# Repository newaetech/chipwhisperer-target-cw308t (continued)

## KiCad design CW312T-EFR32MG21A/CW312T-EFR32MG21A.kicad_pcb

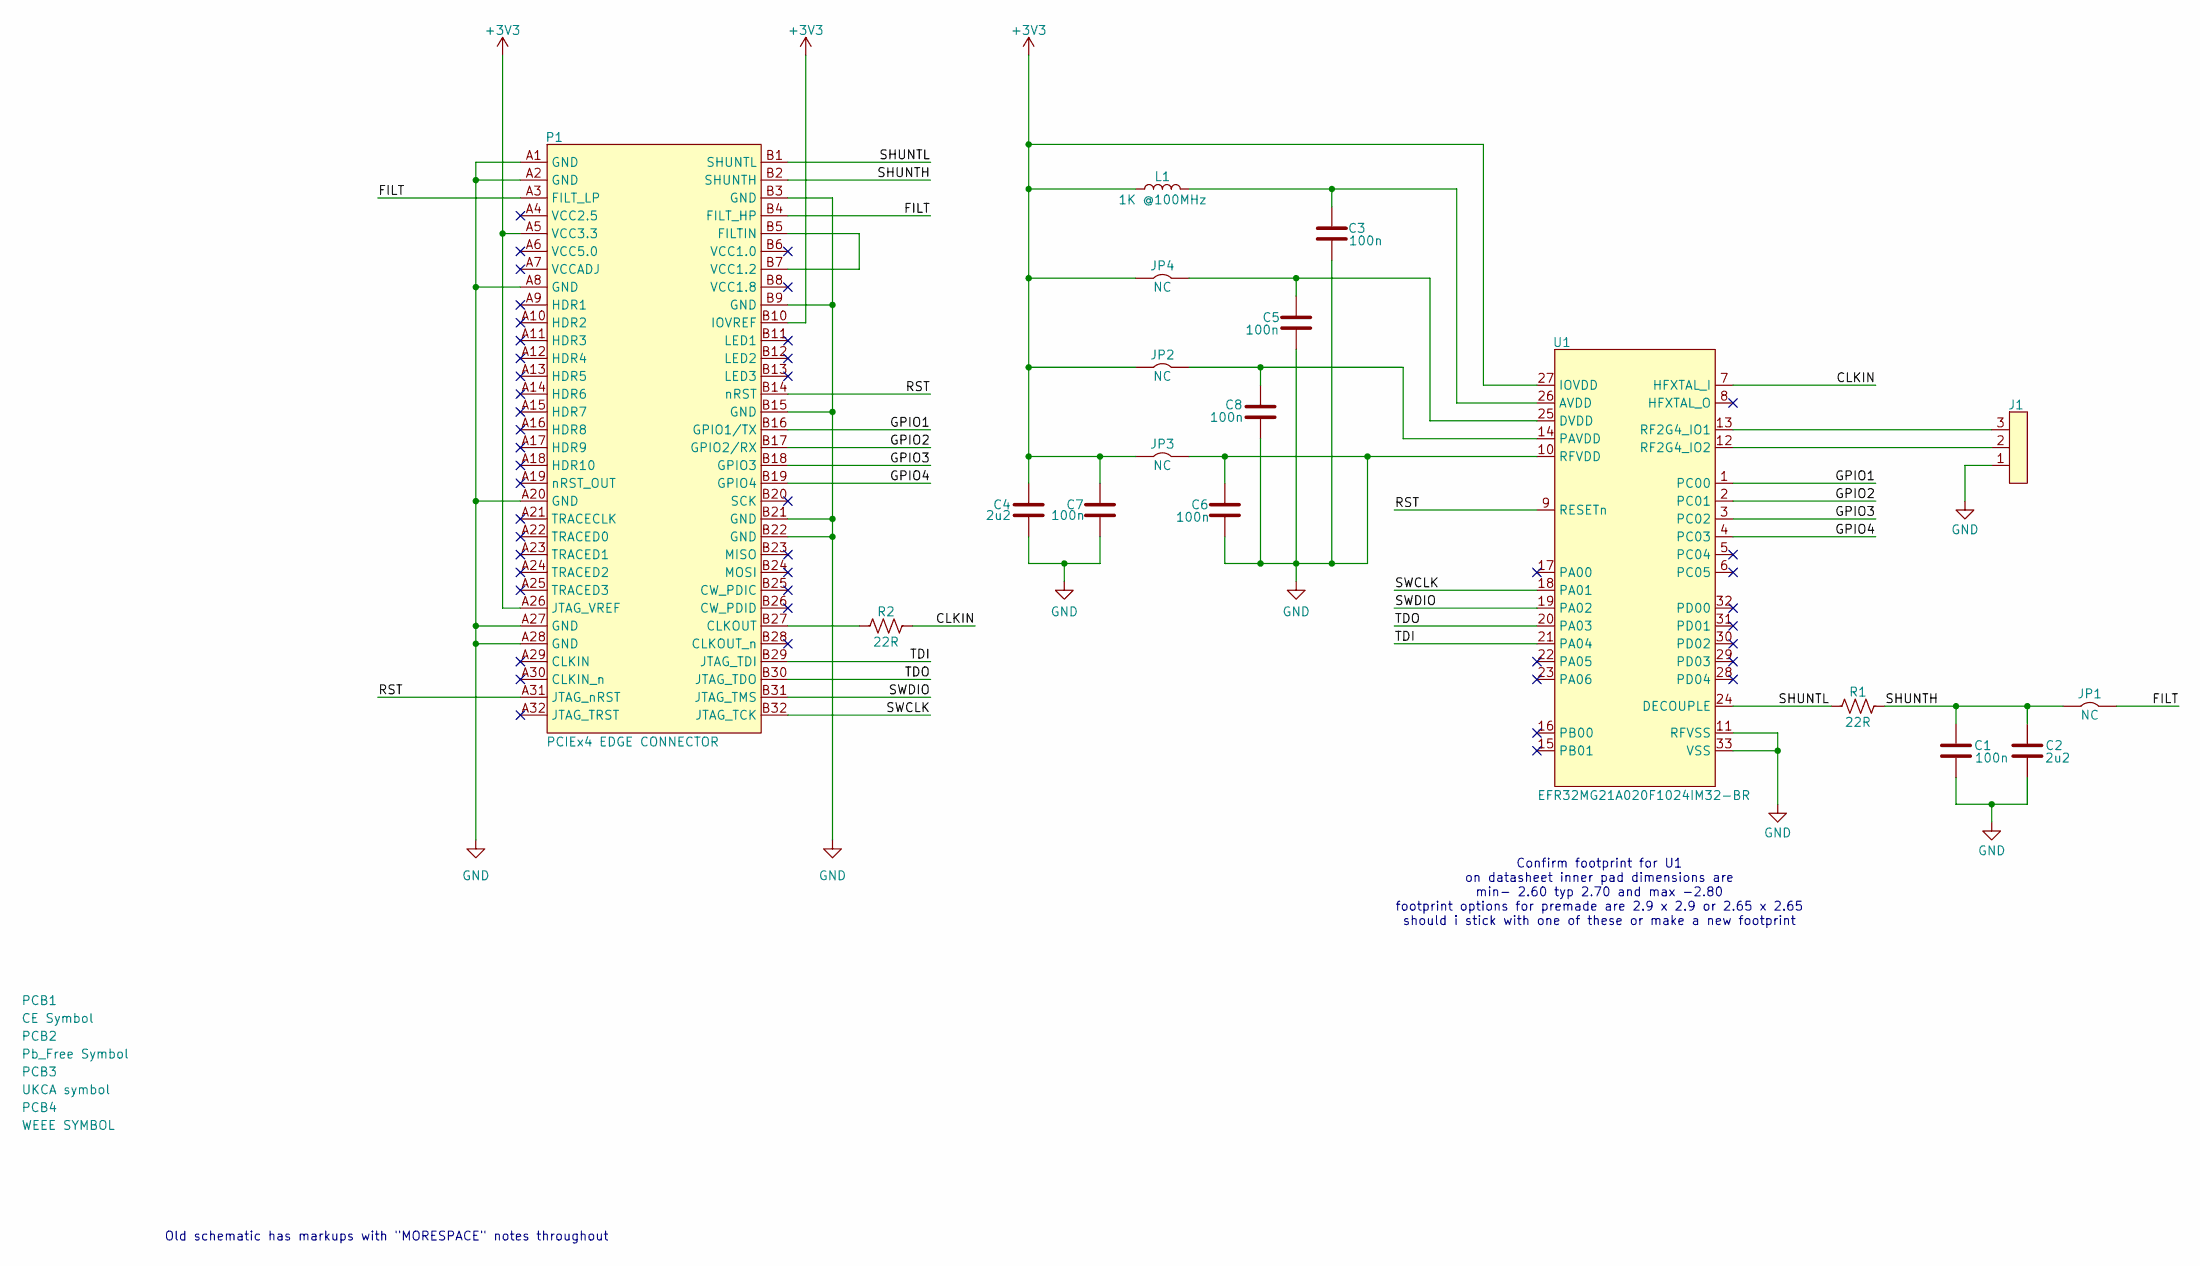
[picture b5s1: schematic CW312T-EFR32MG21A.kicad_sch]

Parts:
C1, C3, C5, C6, C7, C8: CAP_100n_10V_0603; C_0603_1608Metric; Manufacturer Part Number CC0603KRX7R6BB104
C2, C4: CAP_2u2_10V_0603; C_0603_1608Metric; Manufacturer Part Number CC0603KPX7R6BB225
J1: 1x3 straight header pins; PinHeader_1x03_P2.54mm_Vertical; Manufacturer Part Number 61300311121
JP1, JP2, JP3, JP4: SolderJumper-2_P1.3mm_Bridged2Bar_Pad1.0x1.5mm
L1: IND_1K_0603; L_0603_1608Metric; Manufacturer Part Number FBMH1608HM102-T
P1: PCIEx4 EDGE CONNECTOR; CW312_Template
PCB1: CE Symbol; CE-Logo_8.5x6mm_SilkScreen
PCB2: Pb_Free Symbol; Pb_Free_8.0x8.0mm_SilkScreen
PCB3: UKCA symbol; UKCA-Logo_8x8mm_SilkScreen
PCB4: WEEE SYMBOL; WEEE-Logo_5.6x8mm_SilkScreen
R1, R2: RES_22R_0603; R_0603_1608Metric; Manufacturer Part Number RC0603FR-0722RL
U1: EFR32MG21A020F1024IM32-BR; QFN-32-1EP_4x4mm_P0.4mm_EP2.9x2.9mm; Manufacturer Part Number EFR32MG21A020F1024IM32-BR

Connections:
+3V3: C4.2, C7.2, JP2.2, JP3.2, JP4.2, L1.1, P1.A5 (VCC3.3), P1.A26 (JTAG_VREF), P1.B10 (IOVREF), U1.27 (IOVDD)
/CLKIN: R2.2, U1.7 (HFXTAL_I)
/FILT: JP1.1, P1.A3 (FILT_LP), P1.B4 (FILT_HP)
/GPIO1: P1.B16 (GPIO1/TX), U1.1 (PC00)
/GPIO2: P1.B17 (GPIO2/RX), U1.2 (PC01)
/GPIO3: P1.B18 (GPIO3), U1.3 (PC02)
/GPIO4: P1.B19 (GPIO4), U1.4 (PC03)
/RST: P1.A31 (JTAG_nRST), P1.B14 (nRST), U1.9 (RESETn)
/SHUNTH: C1.2, C2.2, JP1.2, P1.B2 (SHUNTH), R1.2
/SHUNTL: P1.B1 (SHUNTL), R1.1, U1.24 (DECOUPLE)
/SWCLK: P1.B32 (JTAG_TCK), U1.18 (PA01)
/SWDIO: P1.B31 (JTAG_TMS), U1.19 (PA02)
/TDI: P1.B29 (JTAG_TDI), U1.21 (PA04)
/TDO: P1.B30 (JTAG_TDO), U1.20 (PA03)
GND: C1.1, C2.1, C3.1, C4.1, C5.1, C6.1, C6.2, C7.1, C8.1, J1.1, JP3.1, P1.A1 (GND), P1.A2 (GND), P1.A8 (GND), P1.A20 (GND), P1.A27 (GND), P1.A28 (GND), P1.B3 (GND), P1.B9 (GND), P1.B15 (GND), P1.B21 (GND), P1.B22 (GND), U1.10 (RFVDD), U1.11 (RFVSS), U1.33 (VSS)
unnamed: P1.B27 (CLKOUT), R2.1
unnamed: P1.B5 (FILTIN), P1.B7 (VCC1.2)
unnamed: C3.2, L1.2, U1.26 (AVDD)
unnamed: C5.2, JP4.1, U1.25 (DVDD)
unnamed: C8.2, JP2.1, U1.14 (PAVDD)
unnamed: J1.3, U1.13 (RF2G4_IO1)
unnamed: J1.2, U1.12 (RF2G4_IO2)

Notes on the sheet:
Old schematic has markups with "MORESPACE" notes throughout
Confirm footprint for U1 on datasheet inner pad dimensions are min- 2.60 typ 2.70 and max -2.80 footprint options for premade are 2.9 x 2.9 or 2.65 x 2.65 should i stick with one of these or make a new footprint

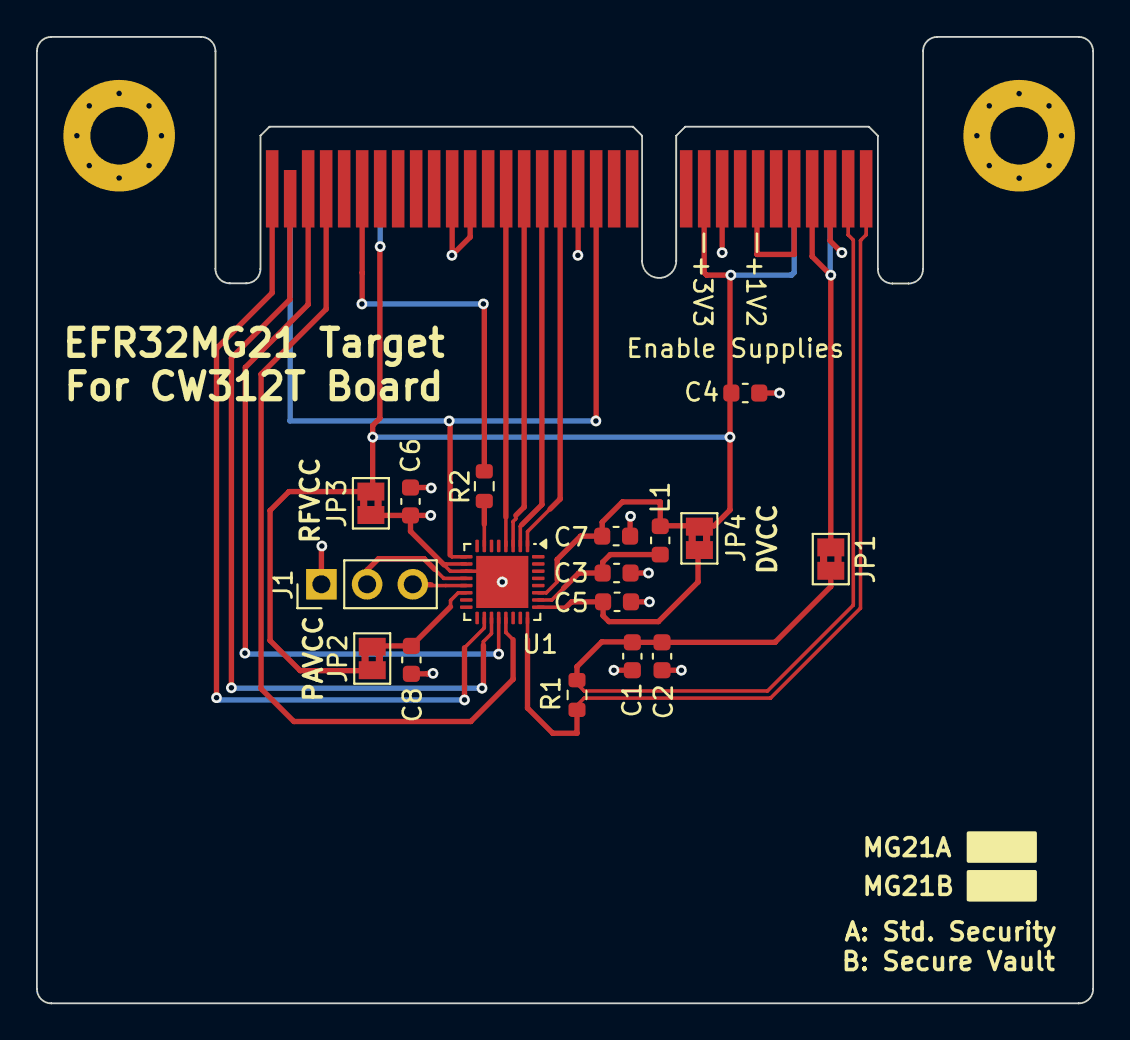
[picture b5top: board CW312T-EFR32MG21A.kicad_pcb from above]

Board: 2 copper layers, 58.7 x 53.7 mm, 22 parts (0 on the bottom side), 22 nets.

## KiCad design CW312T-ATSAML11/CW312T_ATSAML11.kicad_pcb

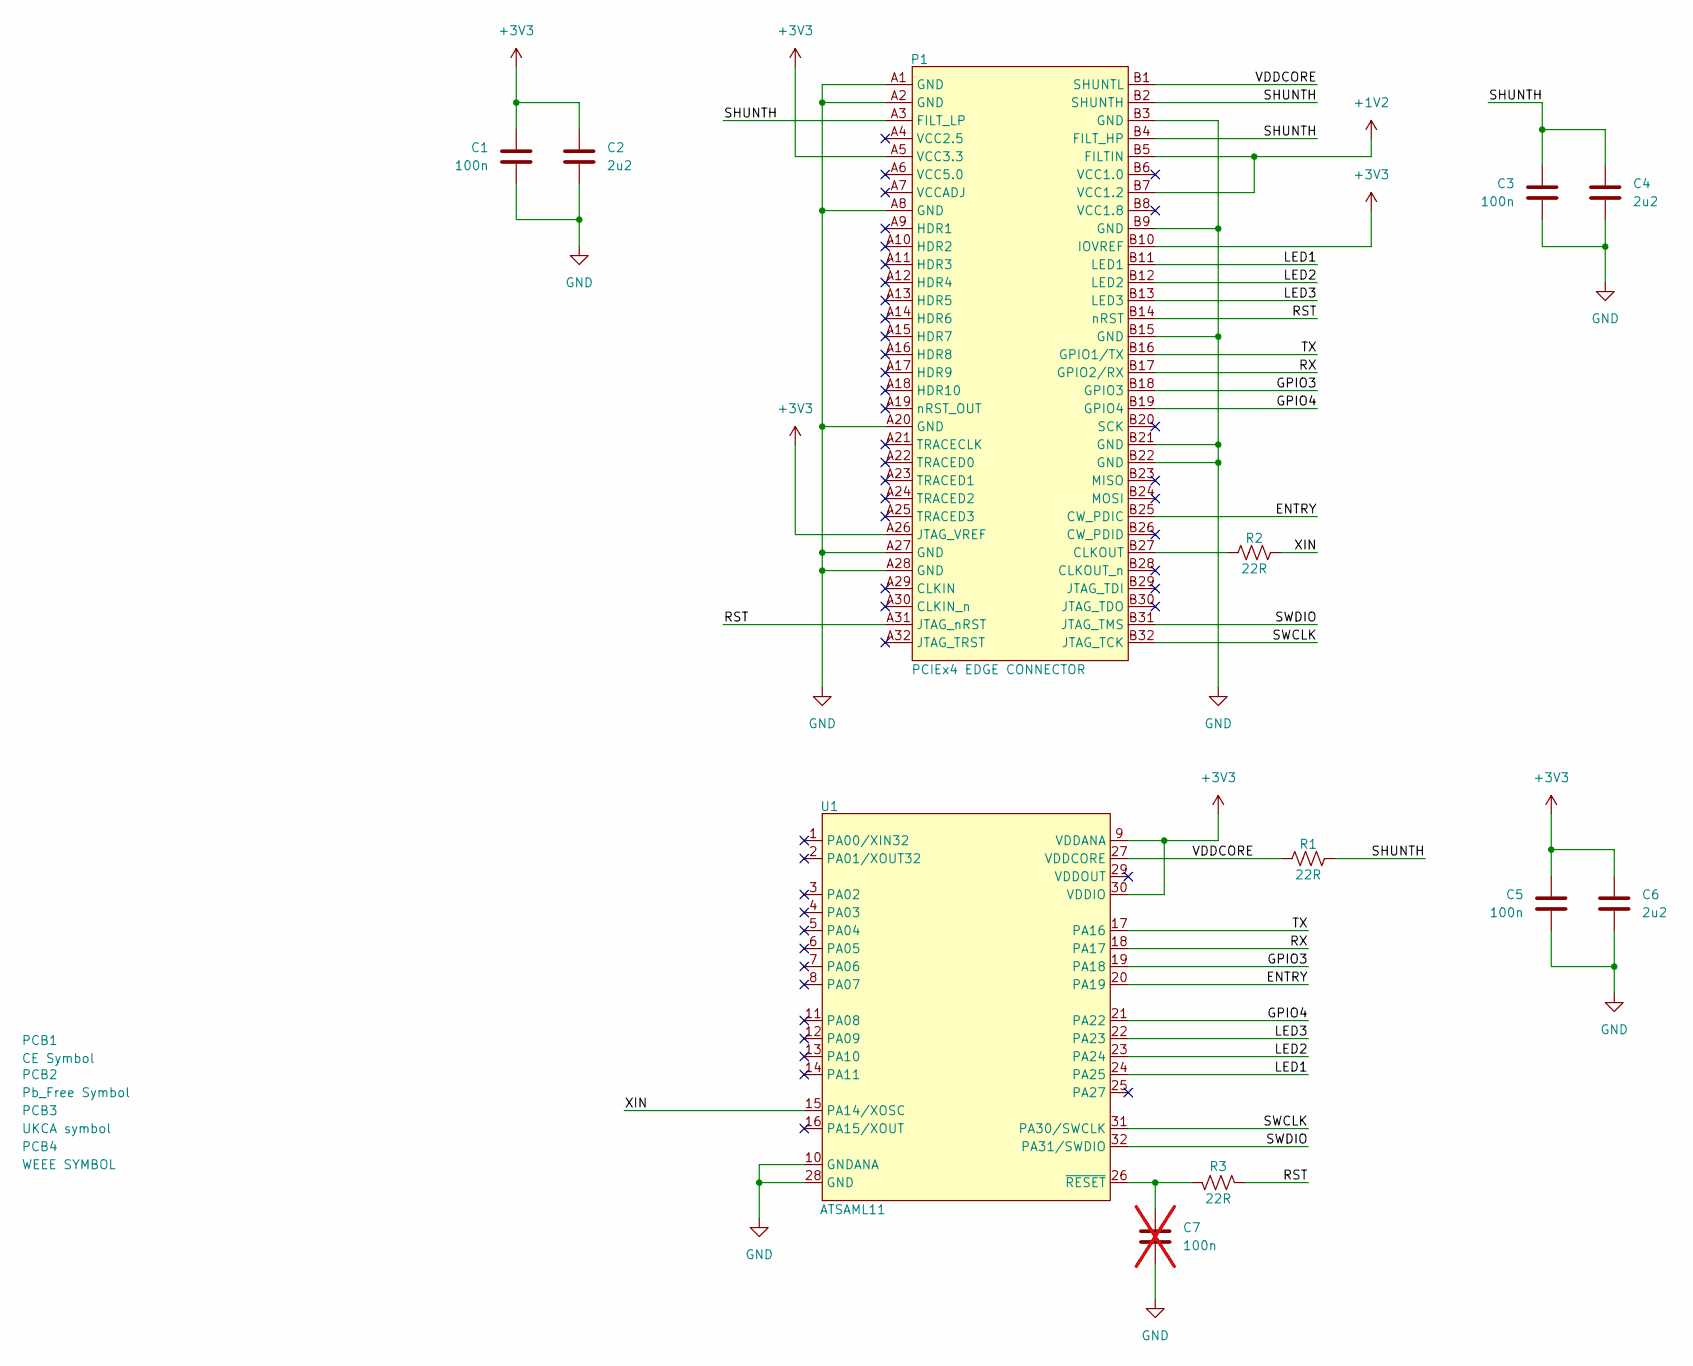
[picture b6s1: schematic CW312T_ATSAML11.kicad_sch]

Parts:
C1, C3, C5: CAP_100n_50V_0603; C_0603_1608Metric; Manufacturer Part Number C0603C104M5RACTU
C2, C4, C6: CAP_2u2_16V_0603; C_0603_1608Metric; Manufacturer Part Number C0603C225K4PAC7867
C7: CAP_100n_50V_0603; C_0603_1608Metric; Manufacturer Part Number C0603C104M5RACTU; not fitted
P1: PCIEx4 EDGE CONNECTOR; CW312_Template
PCB1: CE Symbol; CE-Logo_8.5x6mm_SilkScreen
PCB2: Pb_Free Symbol; Pb_Free_8.0x8.0mm_SilkScreen
PCB3: UKCA symbol; UKCA-Logo_8x8mm_SilkScreen
PCB4: WEEE SYMBOL; WEEE-Logo_5.6x8mm_SilkScreen
R1, R2, R3: 22R_0603; R_0603_1608Metric; Manufacturer Part Number RC0603JR-0722RL
U1: ATSMAL11E16A-AU; TQFP-32_7x7mm_P0.8mm; Manufacturer Part Number ATSAML11E16A-AU

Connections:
+1V2: P1.B5 (FILTIN), P1.B7 (VCC1.2)
+3V3: C1.1, C2.1, C5.1, C6.1, P1.A5 (VCC3.3), P1.A26 (JTAG_VREF), P1.B10 (IOVREF), U1.9 (VDDANA), U1.30 (VDDIO)
/ENTRY: P1.B25 (CW_PDIC), U1.20 (PA19)
/GPIO3: P1.B18 (GPIO3), U1.19 (PA18)
/GPIO4: P1.B19 (GPIO4), U1.21 (PA22)
/LED1: P1.B11 (LED1), U1.24 (PA25)
/LED2: P1.B12 (LED2), U1.23 (PA24)
/LED3: P1.B13 (LED3), U1.22 (PA23)
/RST: P1.A31 (JTAG_nRST), P1.B14 (nRST), R3.2
/RX: P1.B17 (GPIO2/RX), U1.18 (PA17)
/SHUNTH: C3.1, C4.1, P1.A3 (FILT_LP), P1.B2 (SHUNTH), P1.B4 (FILT_HP), R1.2
/SWCLK: P1.B32 (JTAG_TCK), U1.31 (PA30/SWCLK)
/SWDIO: P1.B31 (JTAG_TMS), U1.32 (PA31/SWDIO)
/TX: P1.B16 (GPIO1/TX), U1.17 (PA16)
/VDDCORE: P1.B1 (SHUNTL), R1.1, U1.27 (VDDCORE)
/XIN: R2.2, U1.15 (PA14/XOSC)
GND: C1.2, C2.2, C3.2, C4.2, C5.2, C6.2, C7.2, P1.A1 (GND), P1.A2 (GND), P1.A8 (GND), P1.A20 (GND), P1.A27 (GND), P1.A28 (GND), P1.B3 (GND), P1.B9 (GND), P1.B15 (GND), P1.B21 (GND), P1.B22 (GND), U1.10 (GNDANA), U1.28 (GND)
unnamed: P1.B27 (CLKOUT), R2.1
unnamed: C7.1, R3.1, U1.26 (~RESET)

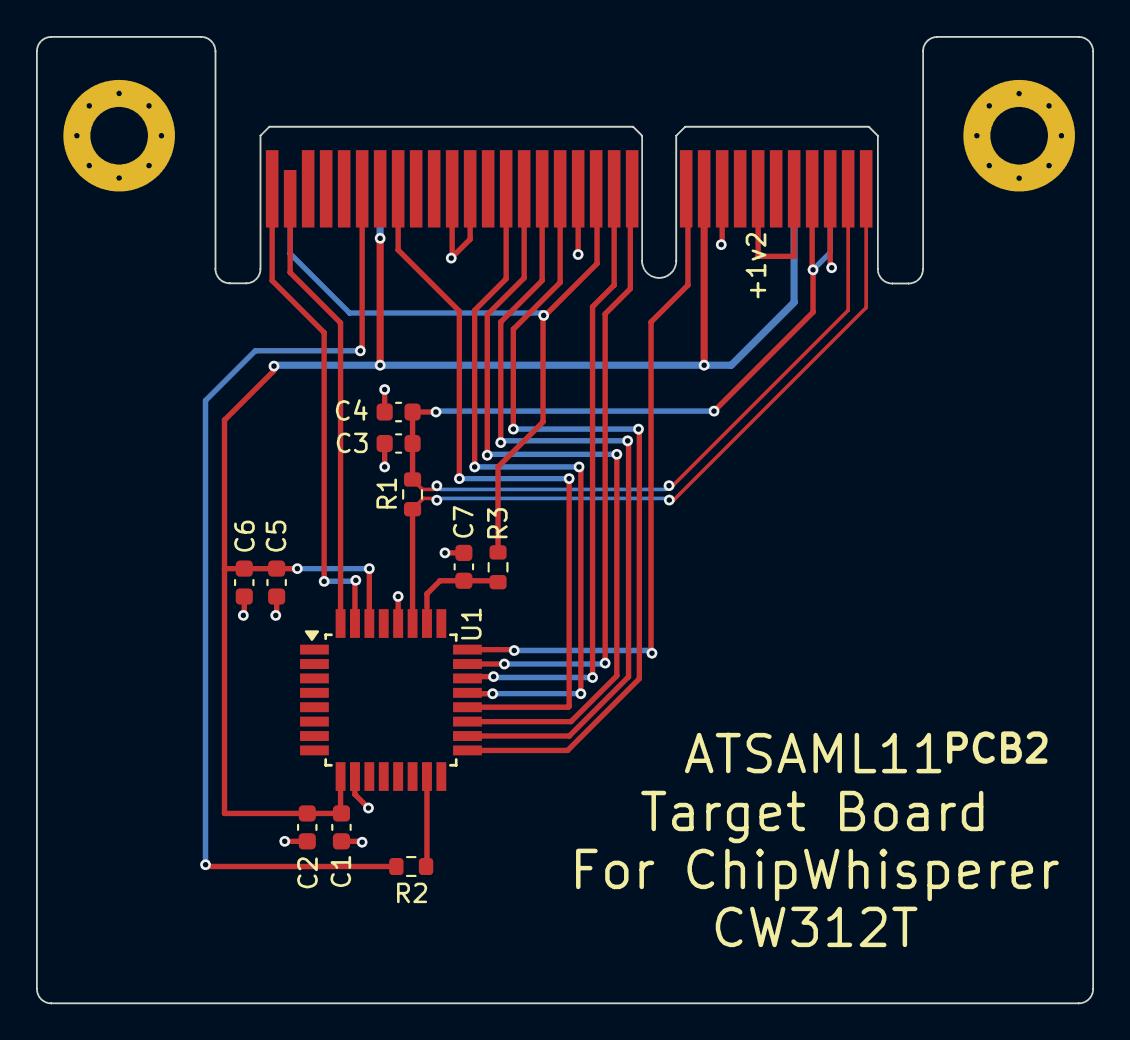
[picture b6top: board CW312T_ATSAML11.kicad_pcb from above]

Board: 2 copper layers, 58.7 x 53.7 mm, 16 parts (0 on the bottom side), 19 nets.

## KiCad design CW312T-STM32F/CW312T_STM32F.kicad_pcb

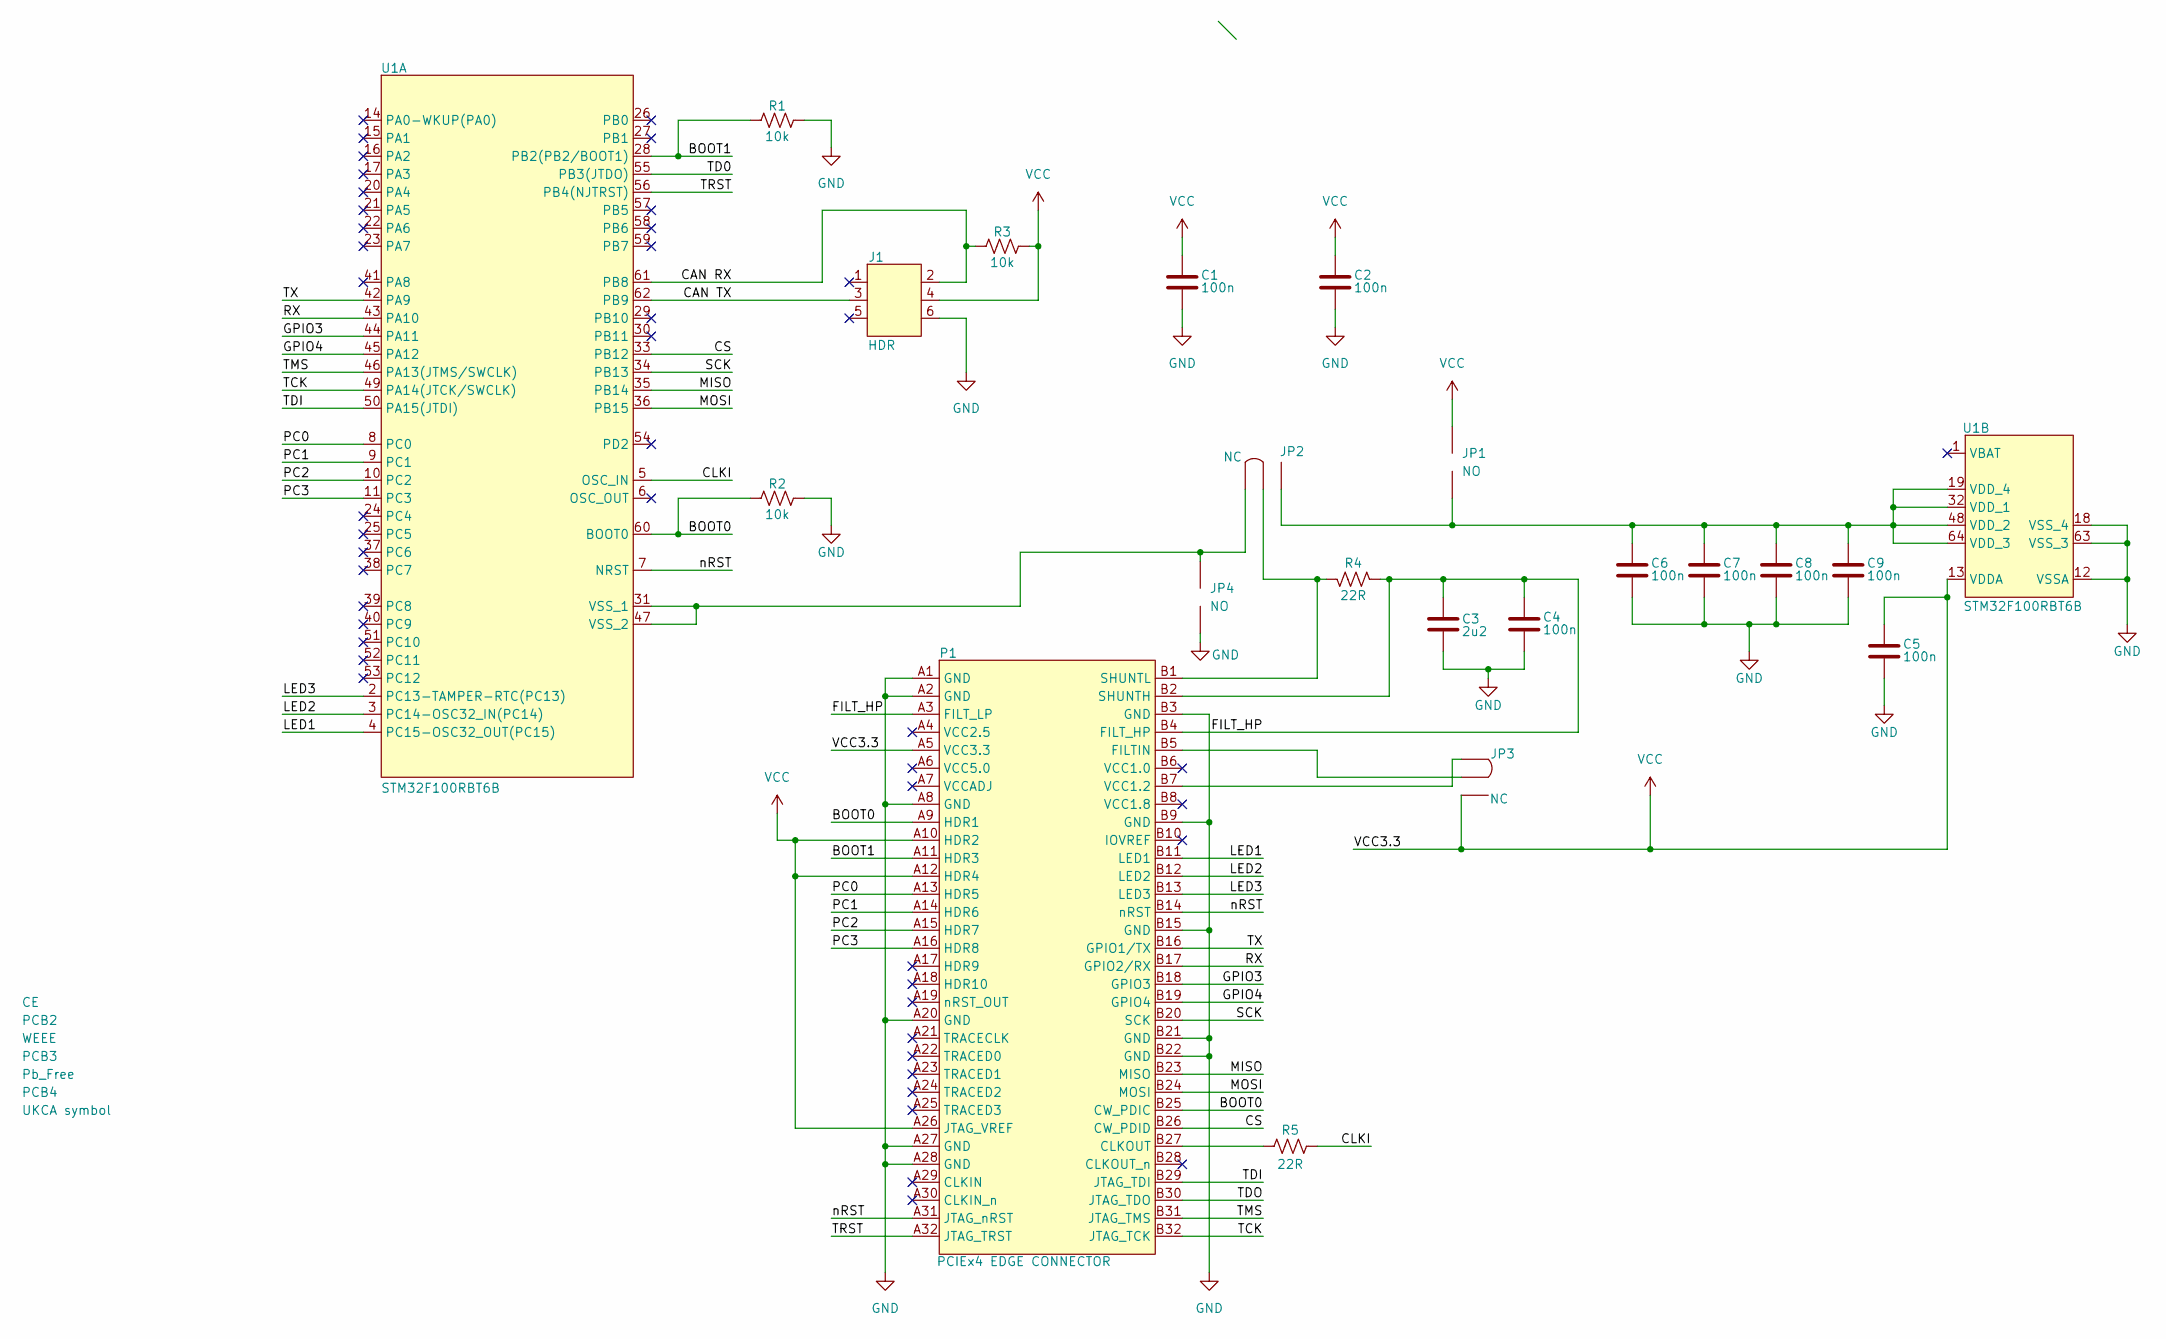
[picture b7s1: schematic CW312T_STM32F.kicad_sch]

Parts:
C1, C2, C4, C5, C6, C7, C8, C9: CAP_100n_25V_0603; C_0603_1608Metric; Manufacturer Part Number CC0603KPX7R8BB104
C3: CAP_2u2_10V_0603; C_0603_1608Metric; Manufacturer Part Number CC0603KPX7R6BB225
J1: HDR_2x3_2.54; PinHeader_2x03_P2.54mm_Vertical; Manufacturer Part Number PH2-06-UA
JP1, JP4: SolderJumper-2_P1.3mm_Open_Pad1.0x1.5mm
JP2, JP3: SolderJumper-3_P1.3mm_Bridged2Bar12_Pad1.0x1.5mm
P1: PCIEx4 EDGE CONNECTOR; CW312_Template
PCB1: CE; CE-Logo_8.5x6mm_SilkScreen
PCB2: WEEE; WEEE-Logo_5.6x8mm_SilkScreen
PCB3: Pb_Free; Pb_Free_8.0x8.0mm_SilkScreen
PCB4: UKCA symbol; UKCA-Logo_8x8mm_SilkScreen
R1, R2, R3: RES_10k_0603; R_0603_1608Metric; Manufacturer Part Number RC0603FR-0710KL
R4: 22R_0603; R_0603_1608Metric; Manufacturer Part Number RC0603JR-0722RL
R5: RES_22R_0603; R_0603_1608Metric; Manufacturer Part Number RC0603FR-0722RL
U1: STM32F100RBT6B; TQFP-64_10x10mm_P0.5mm; Manufacturer Part Number STM32F100RBT6B

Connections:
/BOOT0: P1.A9 (HDR1), P1.B25 (CW_PDIC), R2.1, U1.60 (BOOT0)
/BOOT1: P1.A11 (HDR3), R1.1, U1.28 (PB2(PB2/BOOT1))
/CAN RX: J1.2, R3.1, U1.61 (PB8)
/CAN TX: J1.3, U1.62 (PB9)
/CLKI: R5.2, U1.5 (OSC_IN)
/CS: P1.B26 (CW_PDID), U1.33 (PB12)
/FILT_HP: C3.2, C4.2, P1.A3 (FILT_LP), P1.B2 (SHUNTH), P1.B4 (FILT_HP), R4.2
/GPIO3: P1.B18 (GPIO3), U1.44 (PA11)
/GPIO4: P1.B19 (GPIO4), U1.45 (PA12)
/LED1: P1.B11 (LED1), U1.4 (PC15-OSC32_OUT(PC15))
/LED2: P1.B12 (LED2), U1.3 (PC14-OSC32_IN(PC14))
/LED3: P1.B13 (LED3), U1.2 (PC13-TAMPER-RTC(PC13))
/MISO: P1.B23 (MISO), U1.35 (PB14)
/MOSI: P1.B24 (MOSI), U1.36 (PB15)
/PC0: P1.A13 (HDR5), U1.8 (PC0)
/PC1: P1.A14 (HDR6), U1.9 (PC1)
/PC2: P1.A15 (HDR7), U1.10 (PC2)
/PC3: P1.A16 (HDR8), U1.11 (PC3)
/RX: P1.B17 (GPIO2/RX), U1.43 (PA10)
/SCK: P1.B20 (SCK), U1.34 (PB13)
/TCK: P1.B32 (JTAG_TCK), U1.49 (PA14(JTCK/SWCLK))
/TD0: U1.55 (PB3(JTDO))
/TDI: P1.B29 (JTAG_TDI), U1.50 (PA15(JTDI))
/TDO: P1.B30 (JTAG_TDO)
/TMS: P1.B31 (JTAG_TMS), U1.46 (PA13(JTMS/SWCLK))
/TRST: P1.A32 (JTAG_TRST), U1.56 (PB4(NJTRST))
/TX: P1.B16 (GPIO1/TX), U1.42 (PA9)
/nRST: P1.A31 (JTAG_nRST), P1.B14 (nRST), U1.7 (NRST)
GND: C1.1, C2.1, C3.1, C4.1, C5.1, C6.1, C7.1, C8.1, C9.1, J1.6, JP4.1, P1.A1 (GND), P1.A2 (GND), P1.A8 (GND), P1.A20 (GND), P1.A27 (GND), P1.A28 (GND), P1.B3 (GND), P1.B9 (GND), P1.B15 (GND), P1.B21 (GND), P1.B22 (GND), R1.2, R2.2, U1.12 (VSSA), U1.18 (VSS_4), U1.63 (VSS_3)
unnamed: P1.B27 (CLKOUT), R5.1
unnamed: JP3.2, P1.B5 (FILTIN)
unnamed: JP2.2, P1.B1 (SHUNTL), R4.1
unnamed: JP3.1, P1.B7 (VCC1.2)
unnamed: JP2.1, JP4.2, U1.31 (VSS_1), U1.47 (VSS_2)
unnamed: C6.2, C7.2, C8.2, C9.2, JP1.1, JP2.3, U1.19 (VDD_4), U1.32 (VDD_1), U1.48 (VDD_2), U1.64 (VDD_3)
VCC: C1.2, C2.2, C5.2, J1.4, JP1.2, JP3.3, P1.A5 (VCC3.3), P1.A10 (HDR2), P1.A12 (HDR4), P1.A26 (JTAG_VREF), R3.2, U1.13 (VDDA)

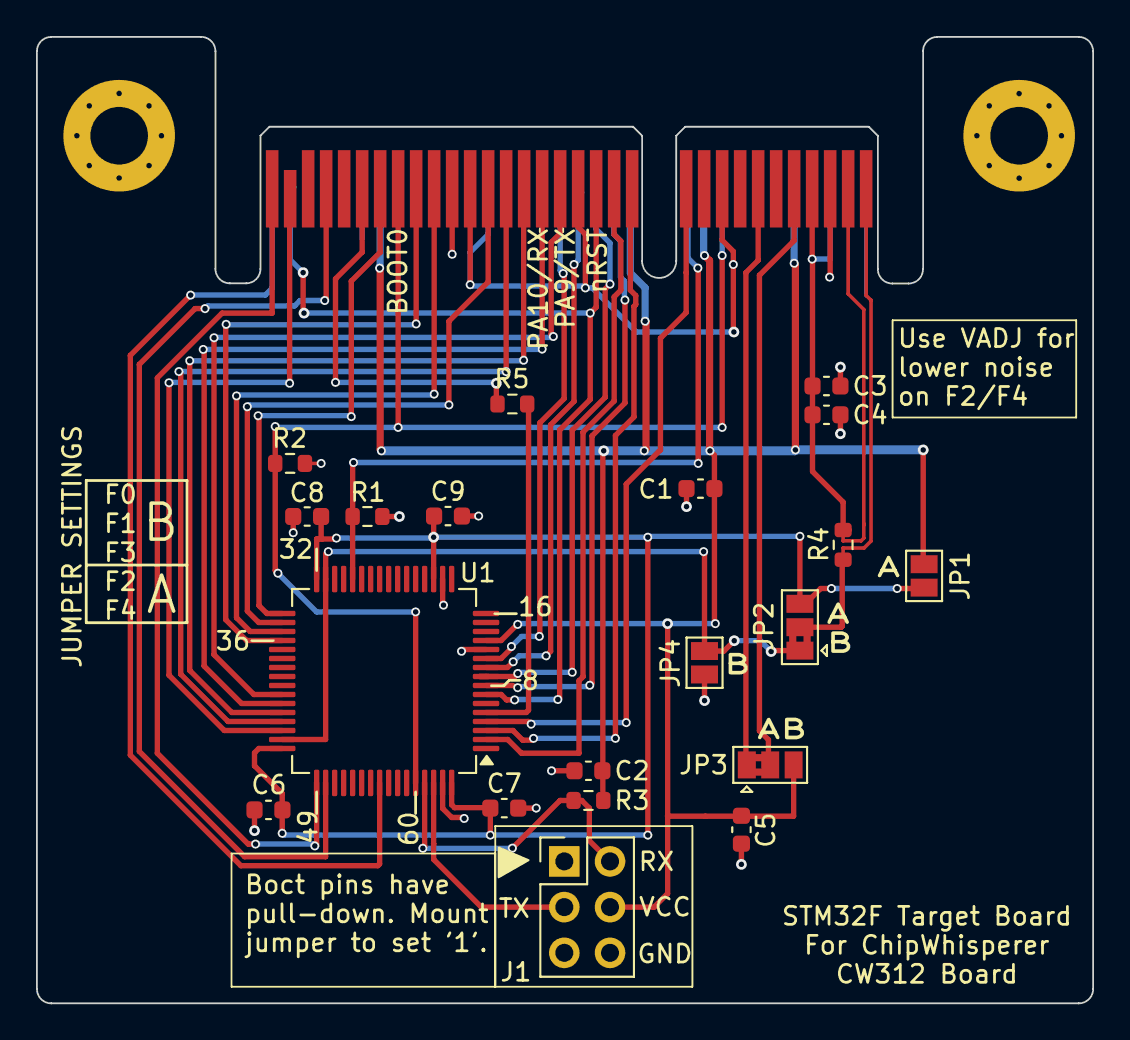
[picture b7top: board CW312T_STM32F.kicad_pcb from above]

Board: 2 copper layers, 58.7 x 53.7 mm, 25 parts (0 on the bottom side), 34 nets.

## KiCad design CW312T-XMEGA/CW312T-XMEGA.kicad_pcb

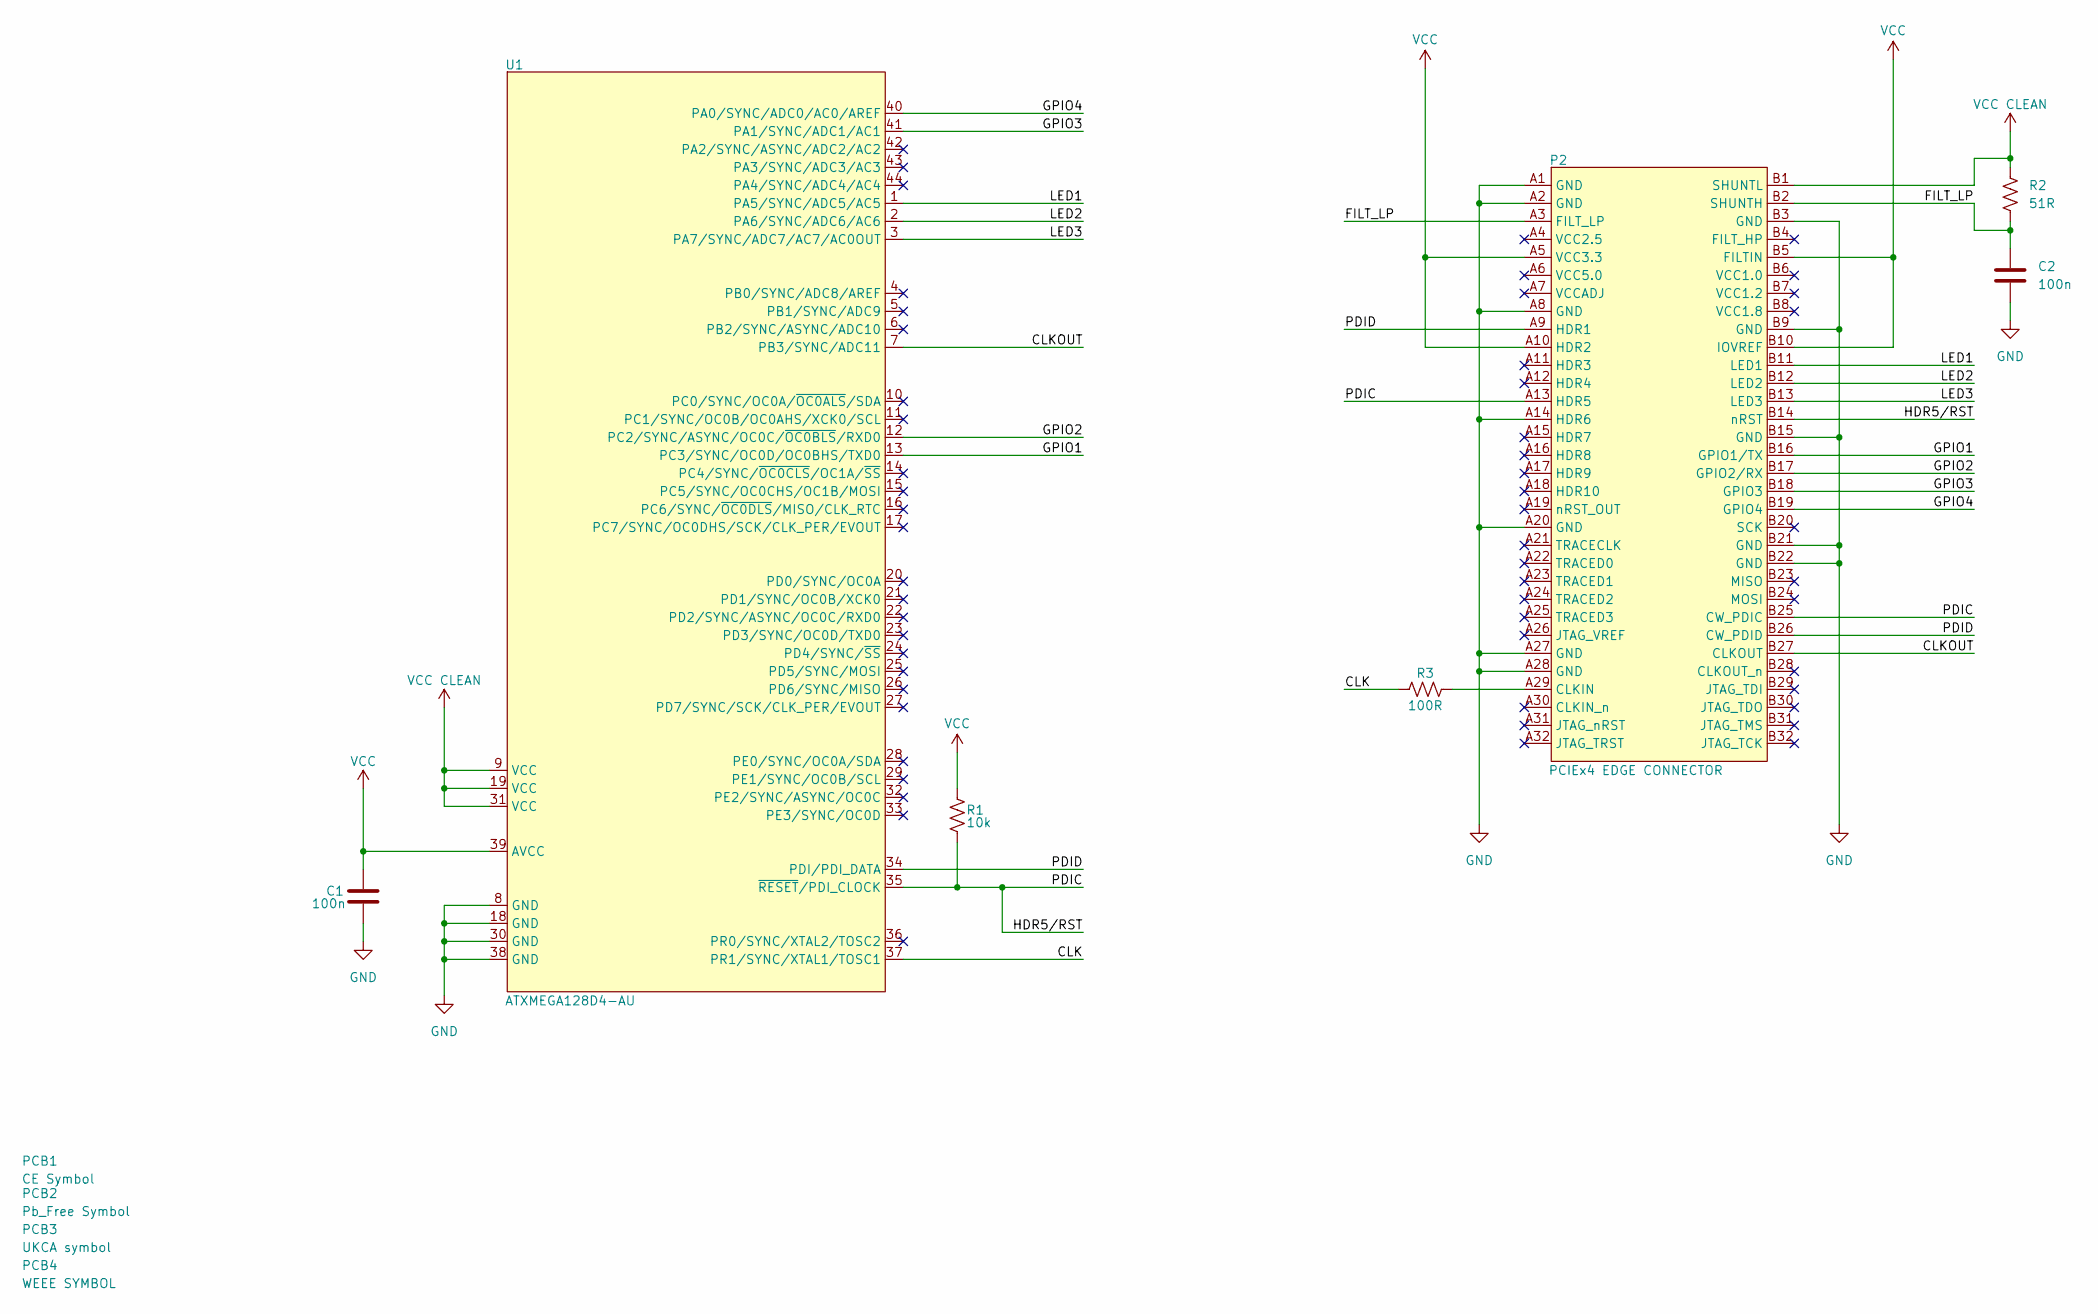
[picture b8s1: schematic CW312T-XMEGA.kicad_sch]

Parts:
C1, C2: CAP_100n_6.3V_0603; C_0603_1608Metric; Manufacturer Part Number CC0603KRX7R5BB104
P2: PCIEx4 EDGE CONNECTOR; CW312_Template
PCB1: CE Symbol; CE-Logo_8.5x6mm_SilkScreen
PCB2: Pb_Free Symbol; Pb_Free_8.0x8.0mm_SilkScreen
PCB3: UKCA symbol; UKCA-Logo_8x8mm_SilkScreen
PCB4: WEEE SYMBOL; WEEE-Logo_5.6x8mm_SilkScreen
R1: RES_10k_0603; R_0603_1608Metric; Manufacturer Part Number RC0603FR-0710KL
R2: RES_51R_0603; R_0603_1608Metric; Manufacturer Part Number RC0603FR-0751RL
R3: RES_100R_0603; R_0603_1608Metric; Manufacturer Part Number RC0603FR-07100RL
U1: ATXMEGA128D4-AU; TQFP-44_10x10mm_P0.8mm; Manufacturer Part Number ATXMEGA128D4-AU

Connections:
/CLK: R3.1, U1.37 (PR1/SYNC/XTAL1/TOSC1)
/CLKOUT: P2.B27 (CLKOUT), U1.7 (PB3/SYNC/ADC11)
/FILT_LP: C2.1, P2.A3 (FILT_LP), P2.B2 (SHUNTH), R2.1
/GPIO1: P2.B16 (GPIO1/TX), U1.13 (PC3/SYNC/OC0D/OC0BHS/TXD0)
/GPIO2: P2.B17 (GPIO2/RX), U1.12 (PC2/SYNC/ASYNC/OC0C/~OC0BLS/RXD0)
/GPIO3: P2.B18 (GPIO3), U1.41 (PA1/SYNC/ADC1/AC1)
/GPIO4: P2.B19 (GPIO4), U1.40 (PA0/SYNC/ADC0/AC0/AREF)
/HDR5/RST: P2.A13 (HDR5), P2.B14 (nRST), P2.B25 (CW_PDIC), R1.1, U1.35 (~RESET/PDI_CLOCK)
/LED1: P2.B11 (LED1), U1.1 (PA5/SYNC/ADC5/AC5)
/LED2: P2.B12 (LED2), U1.2 (PA6/SYNC/ADC6/AC6)
/LED3: P2.B13 (LED3), U1.3 (PA7/SYNC/ADC7/AC7/AC0OUT)
/PDID: P2.A9 (HDR1), P2.B26 (CW_PDID), U1.34 (PDI/PDI_DATA)
GND: C1.1, C2.2, P2.A1 (GND), P2.A2 (GND), P2.A8 (GND), P2.A14 (HDR6), P2.A20 (GND), P2.A27 (GND), P2.A28 (GND), P2.B3 (GND), P2.B9 (GND), P2.B15 (GND), P2.B21 (GND), P2.B22 (GND), U1.8 (GND), U1.18 (GND), U1.30 (GND), U1.38 (GND)
unnamed: P2.A29 (CLKIN), R3.2
VCC: C1.2, P2.A5 (VCC3.3), P2.A10 (HDR2), P2.B5 (FILTIN), P2.B10 (IOVREF), R1.2, U1.39 (AVCC)
VCC CLEAN: P2.B1 (SHUNTL), R2.2, U1.9 (VCC), U1.19 (VCC), U1.31 (VCC)

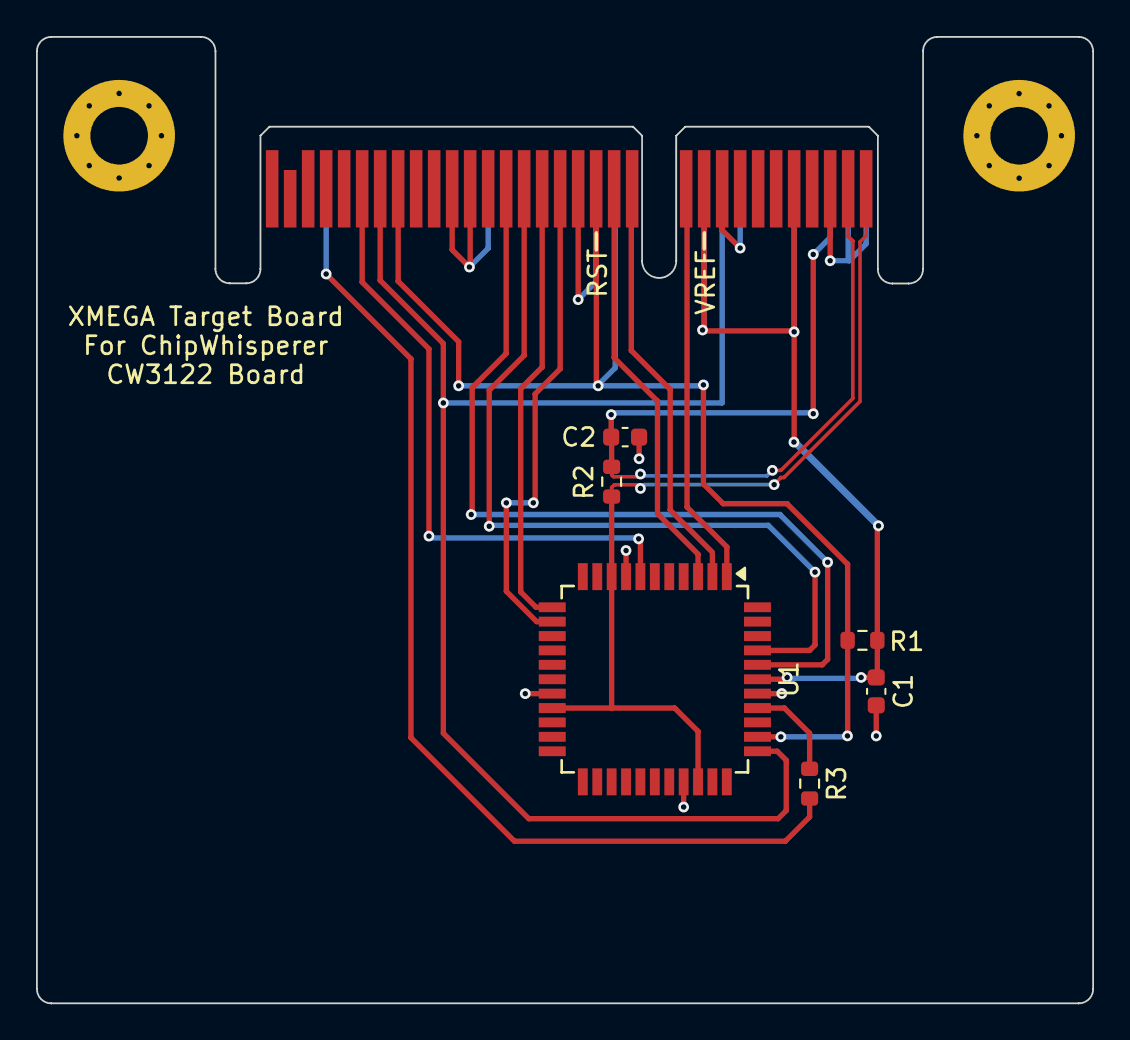
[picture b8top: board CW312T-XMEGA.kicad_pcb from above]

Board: 2 copper layers, 58.7 x 53.7 mm, 11 parts (0 on the bottom side), 16 nets.

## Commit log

2019-03-17 Initial commit - add all files (need PDFs still)
2019-03-17 Add README.md
2019-03-17 Update PDF schematics (not all there yet), gerbers (also not all there yet)
2019-03-17 Remove datasheets etc
2019-03-17 Add photo of baseboard, fix some paths
2019-03-17 Add some pretty photos
2019-03-17 Add ref to wiki
2019-03-18 Add gerbers for K82
2019-05-29 Update project files - will do new PCB gerber update as well
2019-05-29 AURIX: Update to -03 rev, actually works correctly now
2019-05-29 AURIX: Small updates to project file (version number in parameters wasn't bumped)
2019-06-05 -Update targets to reflect PCB release
    -Fix LPC55S69 to disable DC-DC switching reg on Rev -03 PCB and mention mod for -02.
2019-07-11 Add PSOC-62 target
2019-07-30 Add FW310-G002 Target
2019-09-13 Update nrf board
2019-09-23 FE310 board update - will update gerbers etc as well
2019-09-23 Update nRF board layout (rev 03(
2019-09-23 nRF board - rev 03 schematic had incorrect rev # marked. Fix a few minor errors on schematic (left-over flying leads etc)
2019-10-30 Add PSOC62 ordering info, updated schematic now that approved
2020-01-20 Update NRF PCB
2020-01-20 Add imxrt1062 board (NOT TESTED)
2020-01-20 Add MPC5Y Target (MPC5777C)
2020-01-31 Updates to RT1062, NRF, PSOC projects.
2020-02-11 Add MPC5777C target
2020-02-12 Update IMXRT1062 board (need PDF)
2020-02-12 Update RT1062 with PDF sch + correct name of sheets
2020-03-20 Update MP5Y for final release
2020-04-22 Update schematic to match final boards on FE310-G002
2020-05-03 Add EFR32MG21 Target
2020-05-03 Update FE310 silkscreen
2020-05-08 Minor EFM32GG11 updates
2020-05-08 EFR32MG21: Update to -02 version
2020-05-09 EFM32GG11 project file sync
2020-05-09 Add EFR32MG21 socket project (not tested on HW yet)
2020-05-20 Move around files into altium_src directory as needed
2020-06-02 FE310-g002: Change clock resistor values to 100R/330R for better highs-peed
2020-07-01 Add STM32F4-CSP board
2020-07-01 Update PCB to have only chip on 1 side
2020-07-09 Update EFR32MG21
2020-07-29 Add workflow test
2020-07-29 Changing workflow file
2020-07-29 More fixes
2020-07-29 Add - uses: actions/checkout
2020-07-29 More github action work
2020-07-29 Fix execute of entrypoint.sh
2020-07-29 More workflow
2020-07-29 Fix source repo name
2020-07-29 More source fixes...
2020-07-29 Trying to deb
2020-07-29 Add readme
2020-07-29 Debug workflow
2020-07-29 Add readmes (THIS IS WHY WORKFLOW WAS FAILING)
2020-07-29 Trying to make workflow file less terrible
2020-07-29 Fix loop
2020-07-29 Increase debug in workflow
2020-07-29 Workflow debug
2020-07-29 Workflow path fix
2020-07-29 Fix image dir
2020-07-29 Add README etc files
2020-07-29 Rename SAML11 to README.md
2020-07-29 Fix Aurix README
2020-07-29 Attempt to resize that works on mkdocs too
2020-07-29 Fix aurix readme for link
2020-07-29 Update 57 docs
2020-07-29 Fix site links
2020-07-30 Add EFR32MG21, MPC5Y docs
2020-07-30 Fix target name
2020-07-30 Add K82 target docs, minor typo fixes
2020-11-12 HW: STM32F4 WLCSP fix pinout of SMD pins
2020-11-12 HW: Move STM32F415_WLCSP version into correct folder, include gerber outputs
2020-11-25 Add LPC55S69 target
2020-11-25 Fix 55S69 image url
2020-11-26 Add PSoC62
2021-05-02 Add stm32fsocket
2021-06-15 Add STM32F-SOCKET
2021-08-31 Add gerbers for LPC1343
2021-08-31 Add readme for LPC1343 (not in .zip)
2021-09-01 Fix missing GM1 info (was missing on pcbdoc)
2022-01-02 Add generic PCB
2022-01-19 CW308/CW312 board
2022-01-19 Add ice40 CW308
2022-01-24 Add iCE40 for CW312
2022-01-24 Add generic readme, update ice40 readme
2022-01-24 Fix default branch
2022-02-05 Add CW312 targets to RTFM
2022-02-05 Check for folders in script
2022-02-05 3 commits 1 script
2022-02-05 Add ice40 target to rtfm
2022-02-05 Update ice40
2022-02-05 Updated readmes
2022-02-05 Add CW308 ice40 proto
2022-08-05 Add CW312-ATSAM4S Target
2022-08-05 readd documentation for aurix and stm32f3
2022-08-08 Add readme for fe310
2022-08-08 Add images for FE310
2022-08-08 Add fe310 to workflow
2022-08-11 Update ATSAM4S target
2022-08-11 Add SAM4S readme
2022-10-06 Add SAM4S production version
2022-10-06 Add production for ice40 target
2022-11-20 Add CW312 Template for targets
2022-12-09 Add TMP91FW Target
2022-12-09 Update ICE40 PCB
2022-12-09 Update SAM4S sch
2022-12-09 Add K82F design (proto)
2022-12-09 Add K82 readme
2023-01-09 Update cardedge
2023-01-09 Fix STM32F-SOCKET board
2023-01-15 Add XC7A35T Target for CW312
2023-01-15 Add K82F Panel
2023-01-15 Updated ice40 gerbers (not changed, just filesystem sync)
2023-01-15 Add updated CW308-CW312 files
2023-03-01 Add files for rev02 of XC7A35T CW312 Target
2023-03-03 Add Rev3 of PCB
2023-03-04 Update for rev03, fix title sheets, add gerbers
2023-03-23 More sch updates
2023-03-27 Update for DIP switches
2023-03-27 Add 04 rev of XC7A35T
2023-03-27 Sync more XC7A35T files
2023-06-10 Sync a35 outjob
2023-06-10 Add updated K82 design files
2024-04-02 Add nu8051 target board
2024-08-09 Initial RP2350 design files
2024-08-09 Fix gitigore
2024-08-14 add main board schematic
2024-08-14 add pcb_libraries
2024-09-27 Add Fx PCB files, update LPC55s6 programming instructions
2024-12-20 added KiCAD versions of targets
2025-01-28 Add errata to stm32f
2025-02-19 Spell check, fix links.
    NOTE: links corrected so that they work on rtfm.newae.com. Currently
    can't have them be right in both places; picked rtfm.newae.com since
    that's what users are more likely to use. This should be fixed when
    documentation sites are revamped.
2025-02-26 Remove blockquote from headers.
    It doesn't render nicely in jupyterbook, and it prevents that header
    from being part of the ToC.
2025-02-26 Add CW312T_XC7A35T readme.
2025-02-27 Change "attention" boxes for jupyterbook.
    The "!!! attention" style doesn't work for jb.
    Note that neither the old style or the new one we are changing to here
    render on github markdown.
2025-03-02 Fixes for building cleanly on new doc site.
2025-03-03 Update cw/hardware/victims tp cw/firmware.
2025-03-04 fix some external links
2025-03-05 fix links
2025-03-10 Add Ibex link.
